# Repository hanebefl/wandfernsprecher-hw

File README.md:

# GSM Wandfernsprecher
GSM conversion PCB for an old German wall-mounted telephone.

This project uses a SIM800L GSM module, and is controlled by a ESP32-C3 running Micropython.

## Firmware Source Code
The firmware is located in a separate repository: [Wandfernsprecher Firmware](https://github.com/hanebefl/wandfernsprecher-fw)

## Directory Structure
| directory  | content                                                              |
|------------|----------------------------------------------------------------------|
| source     | KiCad project directories                                            |
| production | fabrication files (Gerber, BOM, placement)                           |
| exports    | schematic and layout plots, board 3D model and renderings            |
| datasheets | component datasheets                                                 |
| assets     | board setups, component 3D models, logos                             |
| scripts    | BOM export plugins, miscellaneous helper scripts for file conversion |
| hooks      | git hooks, for example for automatic documentation export            |

## Repository Template
Created with a [KiCAD project template](https://github.com/cyber-murmel/kicad-template) by [cyber-murmel](https://github.com/cyber-murmel)

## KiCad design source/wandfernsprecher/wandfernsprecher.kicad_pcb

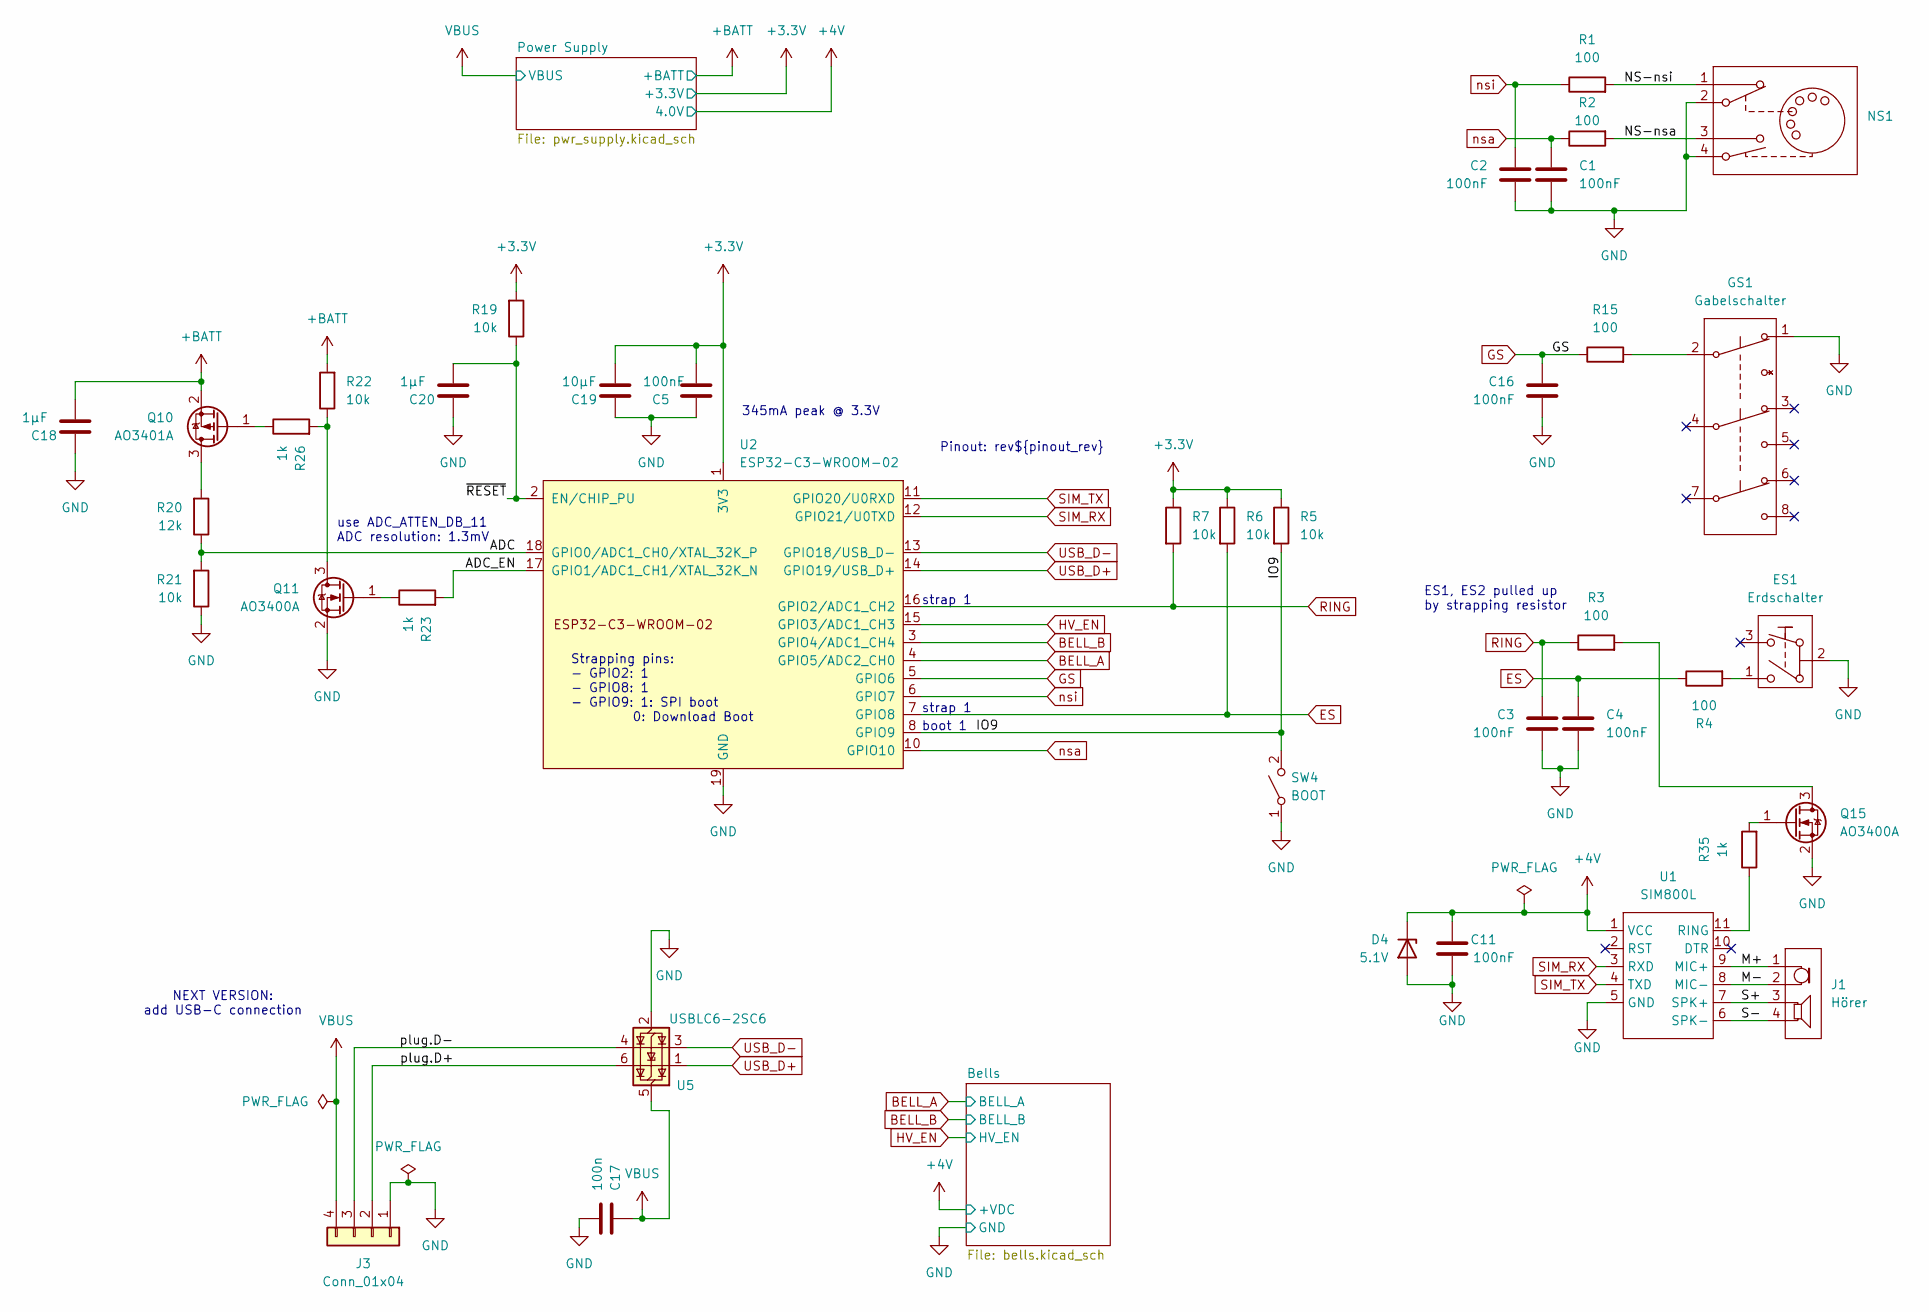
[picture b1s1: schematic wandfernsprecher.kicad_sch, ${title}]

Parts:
C1, C2, C3, C4, C5, C11, C16: 100nF; C_0603_1608Metric
C17: 100n; C_0603_1608Metric
C18, C20: 1µF; C_0603_1608Metric
C19: 10µF; C_0603_1608Metric
D4: 5.1V; D_SOD-123
ES1: Erdschalter; CONN_01x04_vertical_mod
GS1: Gabelschalter
J1: Hörer; CONN_01x04_vertical_mod
J3: Conn_01x04; PinHeader_1x04_P2.54mm_Vertical
NS1: CONN_01x04_vertical_mod
Q10: AO3401A; SOT-23
Q11, Q15: AO3400A; SOT-23
R1, R2, R3, R4, R15: 100; R_0603_1608Metric
R5, R6, R7, R19, R21, R22: 10k; R_0603_1608Metric
R20: 12k; R_0603_1608Metric
R23, R26, R35: 1k; R_0603_1608Metric
SW4: BOOT; SW_PUSH_6mm
U1: SIM800L; SIM800L-module
U2: ESP32-C3-WROOM-02
U5: USBLC6-2SC6; SOT-23-6

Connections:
+3.3V: C5.2, C19.2, R5.1, R6.1, R7.1, R19.2, U2.1 (3V3); also elsewhere on the board
+4V: C11.1, D4.1 (K), U1.1 (VCC); also elsewhere on the board
+BATT: C18.2, Q10.2 (S), R22.2; also elsewhere on the board
/ADC: R20.1, R21.2, U2.18 (GPIO0/ADC1_CH0/XTAL_32K_P)
/ADC_EN: R23.2, U2.17 (GPIO1/ADC1_CH1/XTAL_32K_N)
/IO9: R5.2, SW4.2 (B), U2.8 (GPIO9)
/M+: J1.1 (SPK+), U1.9 (MIC+)
/M-: J1.2 (SPK-), U1.8 (MIC-)
/NS-nsa: NS1.3 (E1), R2.2
/NS-nsi: NS1.1 (N1), R1.2
/S+: J1.3 (MIC+), U1.7 (SPK+)
/S-: J1.4 (MIC-), U1.6 (SPK-)
/plug.D+: J3.2, U5.6 (I/O1)
/plug.D-: J3.3, U5.4 (I/O2)
/~RESET: C20.2, R19.1, U2.2 (EN/CHIP_PU)
BELL_A: U2.4 (GPIO5/ADC2_CH0); also elsewhere on the board
BELL_B: U2.3 (GPIO4/ADC1_CH4); also elsewhere on the board
ES: C4.1, R4.1, R6.2, U2.7 (GPIO8)
GND: C1.2, C2.2, C3.2, C4.2, C5.1, C11.2, C16.2, C17.2, C18.1, C19.1, C20.1, D4.2 (A), ES1.2 (B), GS1.1 (S1l), J3.1, NS1.2 (N2), NS1.4 (E2), Q11.2 (S), Q15.2 (S), R21.1, SW4.1 (A), U1.5 (GND), U2.9 (GND), U2.19 (GND), U5.2 (GND); also elsewhere on the board
GS: C16.1, R15.1, U2.5 (GPIO6)
HV_EN: U2.15 (GPIO3/ADC1_CH3); also elsewhere on the board
unnamed: ES1.1 (A), R4.2
unnamed: GS1.2 (S1c), R15.2
unnamed: Q10.3 (D), R20.2
unnamed: Q10.1 (G), R26.1
unnamed: Q11.3 (D), R22.1, R26.2
unnamed: Q11.1 (G), R23.1
unnamed: Q15.3 (D), R3.2
unnamed: Q15.1 (G), R35.2
unnamed: R35.1, U1.11 (RING)
RING: C3.1, R3.1, R7.2, U2.16 (GPIO2/ADC1_CH2)
SIM_RX: U1.3 (RXD), U2.12 (GPIO21/U0TXD)
SIM_TX: U1.4 (TXD), U2.11 (GPIO20/U0RXD)
USB_D+: U2.14 (GPIO19/USB_D+), U5.1 (I/O1)
USB_D-: U2.13 (GPIO18/USB_D-), U5.3 (I/O2)
VBUS: C17.1, J3.4, U5.5 (VBUS); also elsewhere on the board
nsa: C1.1, R2.1, U2.10 (GPIO10)
nsi: C2.1, R1.1, U2.6 (GPIO7)

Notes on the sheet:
NEXT VERSION: add USB-C connection
Pinout: rev${pinout_rev}
strap 1
boot 1
ES1, ES2 pulled up by strapping resistor
Strapping pins: - GPIO2: 1 - GPIO8: 1 - GPIO9: 1: SPI boot 0: Download Boot
345mA peak @ 3.3V
use ADC_ATTEN_DB_11 ADC resolution: 1.3mV

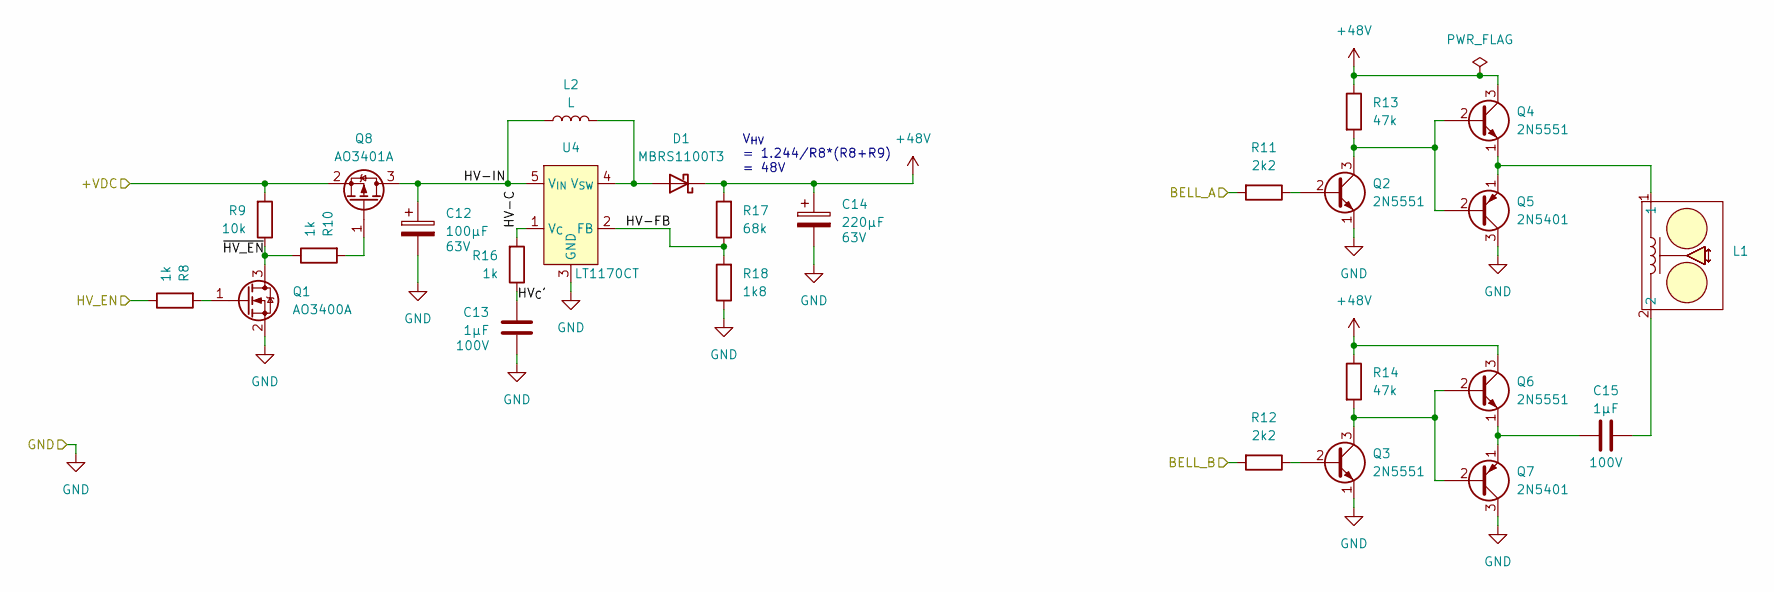
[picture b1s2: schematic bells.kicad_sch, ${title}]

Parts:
C12: 100µF; CP_Radial_D10.0mm_P5.00mm; Voltage 63V
C13: 1µF; C_1210_3225Metric_Pad1.33x2.70mm_HandSolder; Voltage 100V
C14: 220µF; CP_Radial_D10.0mm_P5.00mm; Voltage 63V
C15: 1µF; C_Rect_L18.0mm_W8.0mm_P15.00mm_FKS3_FKP3; Voltage 100V
D1: MBRS1100T3; D_SMB_Handsoldering
L1: CONN_01x02_vertical_mod
L2: L; L_Radial_D12.5mm_P7.00mm_Fastron_09HCP
Q1: AO3400A; SOT-23
Q2, Q3, Q4, Q6: 2N5551; TO-92_HandSolder
Q5, Q7: 2N5401; TO-92_HandSolder
Q8: AO3401A; SOT-23
R8, R10, R16: 1k; R_0603_1608Metric
R9: 10k; R_0603_1608Metric
R11, R12: 2k2; R_0603_1608Metric
R13, R14: 47k; R_0603_1608Metric
R17: 68k; R_0603_1608Metric
R18: 1k8; R_0603_1608Metric
U4: LT1170CT; TO-220-5_P3.4x3.7mm_StaggerOdd_Lead3.8mm_Vertical

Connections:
+4V: Q8.2 (S), R9.2; also elsewhere on the board
+48V: C14.1, D1.1 (K), Q4.3 (C), Q6.3 (C), R13.1, R14.1, R17.2
/Bells/HV-C: R16.2, U4.1 (V_{C})
/Bells/HV-FB: R17.1, R18.2, U4.2 (FB)
/Bells/HV-IN: C12.1, L2.1, Q8.3 (D), U4.5 (V_{IN})
/Bells/HV_{C}': C13.1, R16.1
/Bells/~HV_EN: Q1.3 (D), R9.1, R10.1
BELL_A: R11.2; also elsewhere on the board
BELL_B: R12.2; also elsewhere on the board
GND: C12.2, C13.2, C14.2, Q1.2 (S), Q2.1 (E), Q3.1 (E), Q5.3 (C), Q7.3 (C), R18.1, U4.3 (GND); also elsewhere on the board
HV_EN: R8.1; also elsewhere on the board
unnamed: C15.2, L1.2
unnamed: D1.2 (A), L2.2, U4.4 (V_{SW})
unnamed: Q1.1 (G), R8.2
unnamed: Q2.2 (B), R11.1
unnamed: Q2.3 (C), Q4.2 (B), Q5.2 (B), R13.2
unnamed: Q3.2 (B), R12.1
unnamed: Q3.3 (C), Q6.2 (B), Q7.2 (B), R14.2
unnamed: L1.1, Q4.1 (E), Q5.1 (E)
unnamed: C15.1, Q6.1 (E), Q7.1 (E)
unnamed: Q8.1 (G), R10.2

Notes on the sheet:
V_{HV} = 1.244/R8*(R8+R9) = 48V

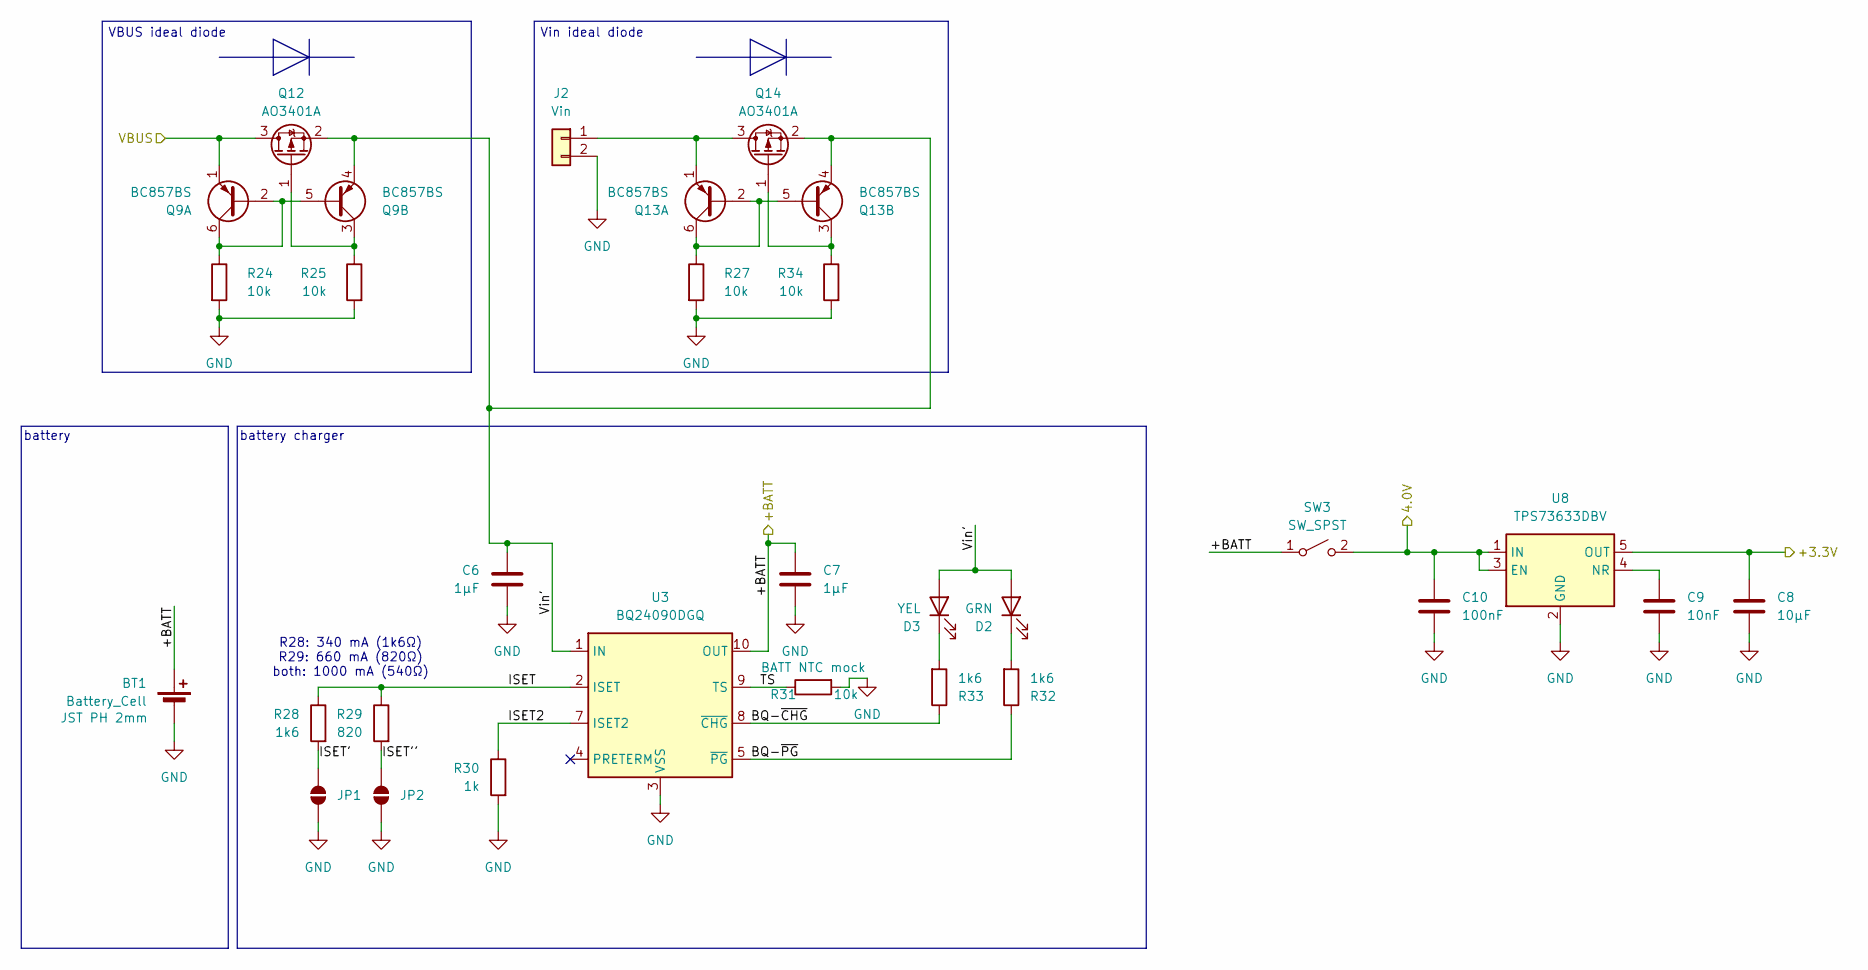
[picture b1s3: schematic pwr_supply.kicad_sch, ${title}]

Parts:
BT1: Battery_Cell; JST_PH_B2B-PH-K_1x02_P2.00mm_Vertical
C6, C7: 1µF; C_0603_1608Metric
C8: 10µF; C_0603_1608Metric
C9: 10nF; C_0603_1608Metric
C10: 100nF; C_0603_1608Metric
D2: GRN; LED_0805_2012Metric
D3: YEL; LED_0805_2012Metric
J2: Vin; JST_PH_B2B-PH-K_1x02_P2.00mm_Vertical
JP1, JP2: SolderJumper_2_Open; SolderJumper-2_P1.3mm_Open_RoundedPad1.0x1.5mm
Q9, Q13: BC857BS; SOT-363_SC-70-6
Q12, Q14: AO3401A; SOT-23
R24, R25, R27, R31, R34: 10k; R_0603_1608Metric
R28, R32, R33: 1k6; R_0603_1608Metric
R29: 820; R_0603_1608Metric
R30: 1k; R_0603_1608Metric
SW3: SW_SPST; JST_PH_B2B-PH-K_1x02_P2.00mm_Vertical
U3: BQ24090DGQ; HVSSOP-10-1EP_3x3mm_P0.5mm_EP1.57x1.88mm_ThermalVias
U8: TPS73633DBV; SOT-23-5

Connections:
+3.3V: C8.1, U8.5 (OUT); also elsewhere on the board
+4V: C10.1, SW3.2 (B), U8.1 (IN), U8.3 (EN); also elsewhere on the board
+BATT: BT1.1 (+), C7.1, SW3.1 (A), U3.10 (OUT); also elsewhere on the board
/Power Supply/BQ-~CHG: R33.1, U3.8 (~CHG)
/Power Supply/BQ-~PG: R32.1, U3.5 (~PG)
/Power Supply/ISET: R28.1, R29.1, U3.2 (ISET)
/Power Supply/ISET2: R30.1, U3.7 (ISET2)
/Power Supply/ISET': JP1.2 (B), R28.2
/Power Supply/ISET'': JP2.2 (B), R29.2
/Power Supply/TS: R31.1, U3.9 (TS)
/Power Supply/Vin': C6.1, D2.2 (A), D3.2 (A), Q9.4 (E2), Q12.2 (S), Q13.4 (E2), Q14.2 (S), U3.1 (IN)
GND: BT1.2 (-), C6.2, C7.2, C8.2, C9.2, C10.2, J2.2, JP1.1 (A), JP2.1 (A), R24.2, R25.2, R27.2, R30.2, R31.2, R34.2, U3.3 (VSS), U3.11 (VSS), U8.2 (GND); also elsewhere on the board
unnamed: D2.1 (K), R32.2
unnamed: D3.1 (K), R33.2
unnamed: J2.1, Q13.1 (E1), Q14.3 (D)
unnamed: Q9.2 (B1), Q9.5 (B2), Q9.6 (C1), R24.1
unnamed: Q9.3 (C2), Q12.1 (G), R25.1
unnamed: Q13.2 (B1), Q13.5 (B2), Q13.6 (C1), R27.1
unnamed: Q13.3 (C2), Q14.1 (G), R34.1
unnamed: C9.1, U8.4 (NR)
VBUS: Q9.1 (E1), Q12.3 (D); also elsewhere on the board

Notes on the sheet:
battery
Vin ideal diode
battery charger
R28: 340 mA (1k6Ω) R29: 660 mA (820Ω) both: 1000 mA (540Ω)
VBUS ideal diode

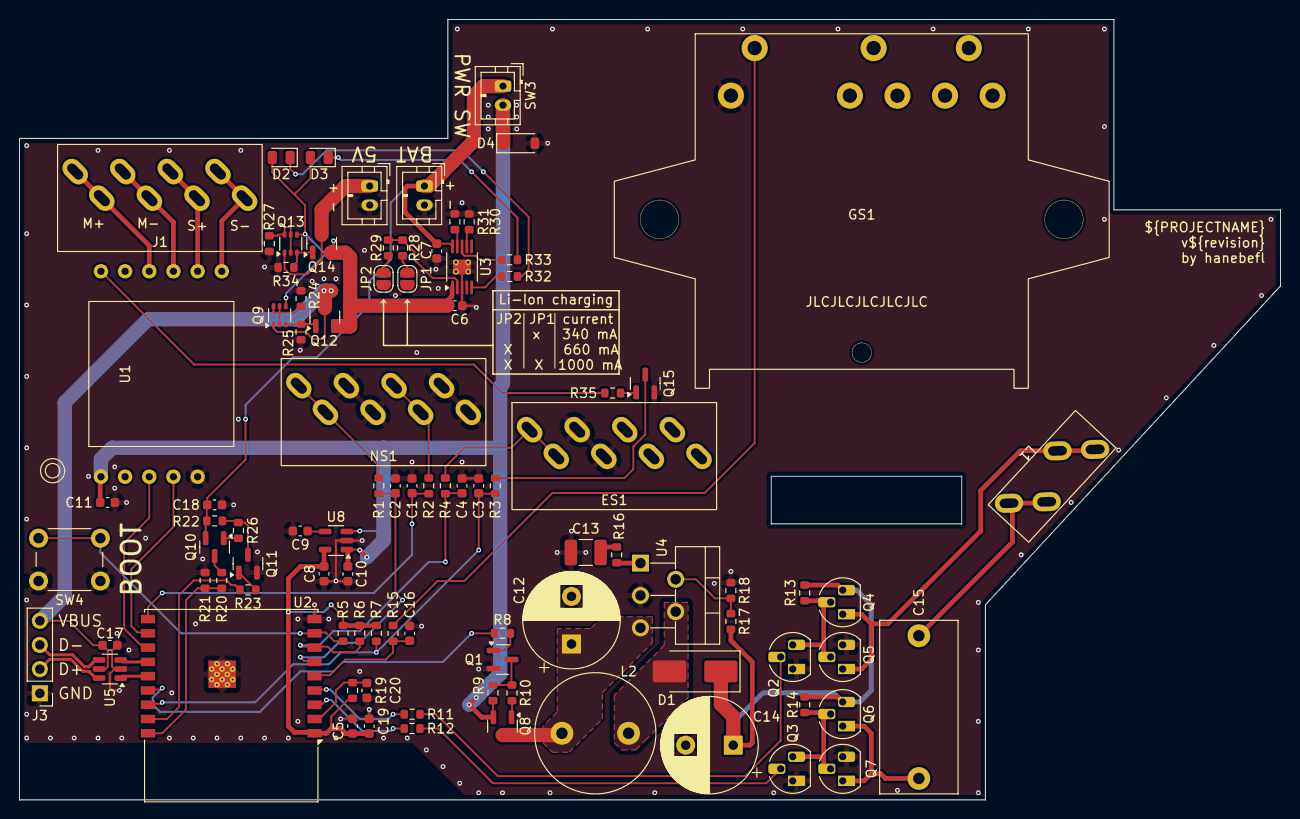
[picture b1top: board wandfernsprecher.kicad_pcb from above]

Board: 4 copper layers, 132.5 x 82.0 mm, 93 parts (0 on the bottom side), 70 nets.

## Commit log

2024-10-05 added espressif kicad-libraries moved source to subfolder for make process added lockfile to .gitignore
2024-10-27 completed layout
2024-10-27 added ibom added switch holder FreeCAD file added Vin header and ideal diodes, finalized layout
2024-11-01 Version 0.1.0
2025-03-02 cleanup and 3D-Models fixed submodule updated README
2025-03-02 Update README.md
    Fixed weblink syntax
2025-03-02 Added MIT License
2025-04-19 connected RING interrupt line from GSM to ESP
2025-04-19 pushed minor version

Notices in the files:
parts and their libraries:
license: Copyright (c) 2025 hanebefl (https://github.com/hanebefl)
